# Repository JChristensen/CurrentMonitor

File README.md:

# Current Monitor
https://github.com/JChristensen/CurrentMonitor  
README file  
Jack Christensen  
Aug-2018

## License
  
Current Monitor by Jack Christensen is licensed under a [Creative Commons Attribution-ShareAlike 4.0 International License](http://creativecommons.org/licenses/by-sa/4.0/).

## Overview
The Current Monitor is an Arduino Uno-compatible board designed to function as a sensor node in an XBee network. While the board was primarily designed to interface to current transformers, it is also general enough to have wider applicability. Features include:
- ATmega328P microcontroller
- interface circuitry for two current transformers
- two analog pins (for current transformers) and four digital pins brought out to screw-type terminal blocks
- three on-board LEDs
- interface circuitry and 3.3V supply for the XBee module
- powered from most any 7-12VDC wall wart with a 2.5mm plug

[Hardware design](https://github.com/JChristensen/CurrentMonitor) and [an Arduino Current Transformer library](https://github.com/JChristensen/CurrentTransformer) are available on GitHub.  
PC boards can be ordered from [OSH Park](https://www.oshpark.com/shared_projects/QCjudQBh).  
A bill of materials is available at [Mouser Electronics](https://www.mouser.com/ProjectManager/ProjectDetail.aspx?State=EDIT&ProjectGUID=d999f360-1612-415f-8324-2acceb9dd570) and also in the [GitHub repo](https://github.com/JChristensen/CurrentMonitor).

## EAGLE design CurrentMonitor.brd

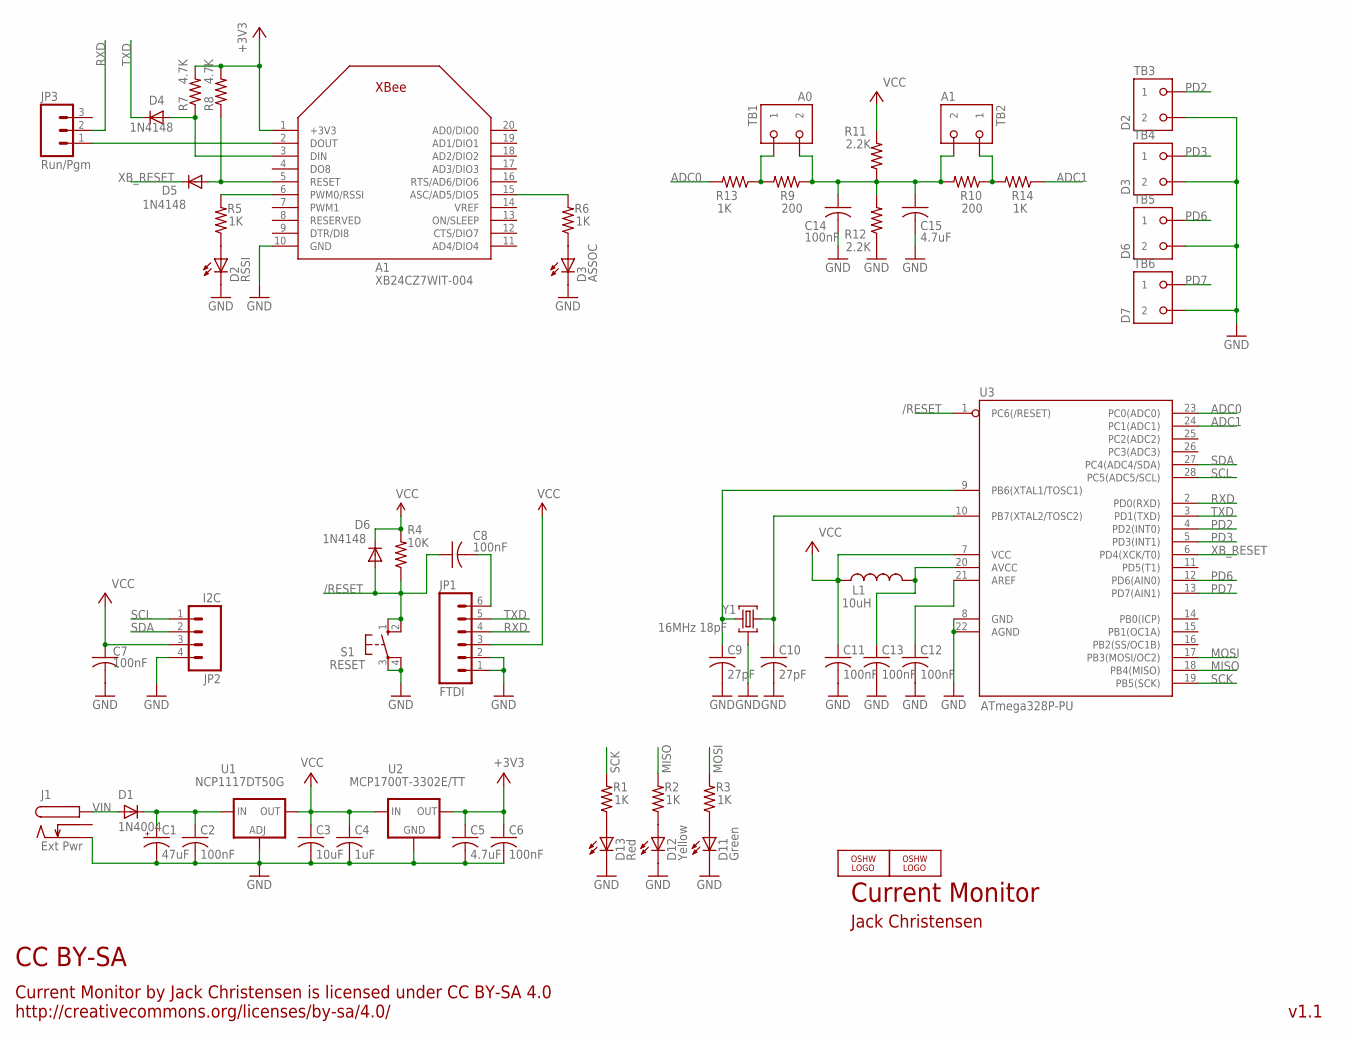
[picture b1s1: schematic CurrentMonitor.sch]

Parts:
A1: XB24CZ7WIT-004; XBEE_OVAL_PADS
C1: 47uF; E5-5
C2, C6, C7, C8, C11, C12, C13, C14: 100nF; M0805
C3: 10uF; M0805
C4: 1uF; M0805
C5, C15: 4.7uF; M0805
C9, C10: 27pF; M0805
D1: 1N4004; 1N400X
D2: RSSI; D0805A
D3: ASSOC; D0805
D4, D5: 1N4148; SOD-323F-A
D6: 1N4148; SOD-323F
D11: Green; D0805
D12: Yellow; D0805
D13: Red; D0805
J1: Ext Pwr; KLDX-0202
JP1: FTDI; 1X06_LOCK
JP2: I2C; 1X04_LOCK
JP3: Run/Pgm; 1X03_LOCK
L1: 10uH; M0805
LOGO1, LOGO2: OSHW_LOGO_8MILX0100-NT; OSHW_8X100_NOTEXT
R1, R2, R3, R5, R6, R13, R14: 1K; M0805
R4: 10K; M0805
R7, R8: 4.7K; M0805
R9, R10: 200; M0805
R11, R12: 2.2K; M0805
S1: RESET; B3F-10XXOCT
TB1: A0; OST-TB-2-3.5MM
TB2: A1; OST-TB-2-3.5MM
TB3: D2; OST-TB-2-3.5MM
TB4: D3; OST-TB-2-3.5MM
TB5: D6; OST-TB-2-3.5MM
TB6: D7; OST-TB-2-3.5MM
U1: NCP1117DT50G; DPACK
U2: MCP1700T-3302E/TT; SOT23-W
U3: ATmega328P-PU; DIL28-3
Y1: 16MHz 18pF; RESONATOR

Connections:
+3V3: A1.1 (+3V3), C5.1, C6.1, R7.2, R8.2, U2.2 (OUT)
/RESET: C8.1, D6.A, R4.1, S1.1 (S), S1.2 (S1), U3.1 (PC6(/RESET))
ADC0: R13.2, U3.23 (PC0(ADC0))
ADC1: R14.1, U3.24 (PC1(ADC1))
GND: A1.10 (GND), C1.-, C2.2, C3.2, C4.2, C5.2, C6.2, C7.2, C9.2, C10.2, C11.2, C12.2, C13.2, C14.2, C15.2, D2.K (C), D3.K (C), D11.K (C), D12.K (C), D13.K (C), J1.P$2, JP1.1, JP1.2, JP2.4, R12.1, S1.3, S1.4 (P1), TB3.P$2 (2), TB4.P$2 (2), TB5.P$2 (2), TB6.P$2 (2), U1.1 (ADJ), U2.1 (GND), U3.8 (GND), U3.22 (AGND), Y1.2
MISO: R2.2, U3.18 (PB4(MISO))
MOSI: R3.2, U3.17 (PB3(MOSI/OC2))
unnamed: D13.A, R1.1
unnamed: D1.A, J1.P$1
unnamed: C14.1, C15.1, R9.1, R10.2, R11.1, R12.2, TB1.P$2 (2), TB2.P$2 (2)
unnamed: C10.1, U3.10 (PB7(XTAL2/TOSC2)), Y1.3
unnamed: C13.1, L1.2, U3.20 (AVCC)
unnamed: C9.1, U3.9 (PB6(XTAL1/TOSC1)), Y1.1
unnamed: C12.1, U3.21 (AREF)
unnamed: A1.3 (DIN), D4.A, R7.1
unnamed: D12.A, R2.1
unnamed: A1.2 (DOUT), JP3.1
unnamed: D2.A, R5.1
unnamed: D3.A, R6.1
unnamed: A1.6 (PWM0/RSSI), R5.2
unnamed: A1.15 (ASC/AD5/DIO5), R6.2
unnamed: R9.2, R13.1, TB1.P$1 (1)
unnamed: R10.1, R14.2, TB2.P$1 (1)
unnamed: A1.5 (RESET), D5.A, R8.1
unnamed: D11.A, R3.1
PD2: TB3.P$1 (1), U3.4 (PD2(INT0))
PD3: TB4.P$1 (1), U3.5 (PD3(INT1))
PD6: TB5.P$1 (1), U3.12 (PD6(AIN0))
PD7: TB6.P$1 (1), U3.13 (PD7(AIN1))
RST: C8.2, JP1.6
RXD: JP1.4, JP3.2, U3.2 (PD0(RXD))
SCK: R1.2, U3.19 (PB5(SCK))
SCL: JP2.1, U3.28 (PC5(ADC5/SCL))
SDA: JP2.2, U3.27 (PC4(ADC4/SDA))
TXD: D4.K, JP1.5, U3.3 (PD1(TXD))
VCC: C3.1, C4.1, C7.1, C11.1, D6.K, JP1.3, JP2.3, L1.1, R4.2, R11.2, U1.4 (OUT), U2.3 (IN), U3.7 (VCC)
VIN: C1.+, C2.1, D1.K, U1.3 (IN)
XB_RESET: D5.K, U3.6 (PD4(XCK/T0))

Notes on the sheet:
Current Monitor
Jack Christensen
Current Monitor by Jack Christensen is licensed under CC BY-SA 4.0 http://creativecommons.org/licenses/by-sa/4.0/
CC BY-SA
v1.1

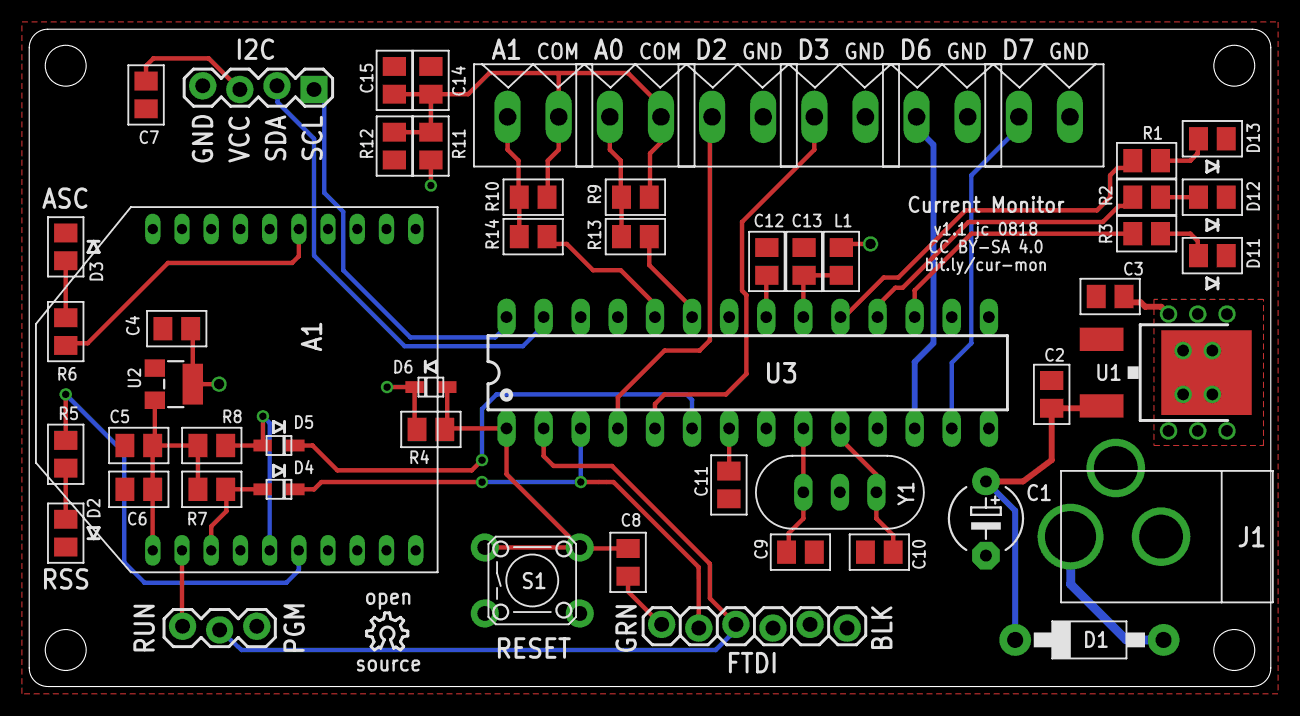
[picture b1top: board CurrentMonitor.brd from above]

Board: 2 copper layers, 85.0 x 45.0 mm, 57 parts (1 on the bottom side), 38 nets.

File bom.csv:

Current Monitor,,,,,
Bill of materials,,,,,
https://www.mouser.com/ProjectManager/ProjectDetail.aspx?Acc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,,,,,
,,,,,
Part No.,Order Qty.,Mouser #,Mfr. #,Manufacturer,Description
A1,2,855-M22-7131042,M22-7131042,Harwin,Headers & Wire Housings 10 PIN SIL VERTICAL GOLD+TIN SOCKET
A1,1,888-XB24CZ7WIT-004,XB24CZ7WIT-004,Digi International,Zigbee Modules (802.15.4) XBee ZB S2C TH Wire Antenna
C1,1,667-ECA-1CM470B,ECA-1CM470B,Panasonic,Aluminum Electrolytic Capacitors - Radial Leaded Al Lytic Cap 85C Radial M Series
"C2, C6, C7, C8, C11-14",8,581-08053C104K,08053C104KAT2A,AVX,Multilayer Ceramic Capacitors MLCC - SMD/SMT 25V .1uF X7R 0805 10%
C3,1,963-LMK212BJ106KG-T,LMK212BJ106KG-T,Taiyo Yuden,Multilayer Ceramic Capacitors MLCC - SMD/SMT 10uF 10V X5R +/-10% 0805 Gen Purp
C4,1,81-GRM21BR61C105KA1K,GRM21BR61C105KA01K,Murata,Multilayer Ceramic Capacitors MLCC - SMD/SMT 1uf 16V X5R +/-10% 0805
"C5, C15",2,963-LMK212B7475KG-T,LMK212B7475KG-T,Taiyo Yuden,Multilayer Ceramic Capacitors MLCC - SMD/SMT 4.7uF 10V X7R +/-10% 0805 Gen Purp
"C9, C10",2,603-CC805JRNPO9BN270,CC0805JRNPO9BN270,Yageo,Multilayer Ceramic Capacitors MLCC - SMD/SMT 27pF 50V NPO 5%
D1,1,863-1N4004G,1N4004G,ON Semiconductor,Rectifiers 400V 1A Standard
D12,1,859-LTST-C171KSKT,LTST-C171KSKT,Lite-On,Standard LEDs - SMD Yellow Clear 587nm
"D2, D13",2,859-LTST-C171KRKT,LTST-C171KRKT,Lite-On,Standard LEDs - SMD Red Clear 55MCD
"D3, D11",2,859-LTST-C171KGKT,LTST-C171KGKT,Lite-On,Standard LEDs - SMD Green Clear 571nm
"D4, D5, D6",3,512-1N4148WS,1N4148WS,ON Semiconductor,"Diodes - General Purpose, Power, Switching Small Signal Diode"
J1,1,806-KLDX-0202-B,KLDX-0202-B,Kycon,DC Power Connectors 2.5mm PCB JACK POWER JACK
JP1,1,,,,"0.1” Header, male, 6-position"
JP2,1,,,,"0.1” Header, female, 4-position"
JP3,1,,,,"0.1” Header, male, 3-position"
JP3,1,,,,Shorting block for 0.1” header
L1,1,963-LBR2012T100K,LBR2012T100K,Taiyo Yuden,Fixed Inductors 0805 10uH 468mOhms +/-10%Tol 150mA
"R1-3, R5-6, R13-14",7,603-RC0805FR-071KL,RC0805FR-071KL,Yageo,Thick Film Resistors - SMD 1K OHM 1%
"R11, R12",2,603-RC0805FR-072K2L,RC0805FR-072K2L,Yageo,Thick Film Resistors - SMD 2.2K OHM 1%
R4,1,603-RC0805FR-1310KL,RC0805FR-1310KL,Yageo,Thick Film Resistors - SMD 10K OHM 1%
"R7, R8",2,603-RC0805FR-074K7L,RC0805FR-074K7L,Yageo,Thick Film Resistors - SMD 4.7K OHM 1%
"R9, R10",2,603-RC0805FR-07200RL,RC0805FR-07200RL,Yageo,Thick Film Resistors - SMD 200 OHM 1%
S1,1,653-B3F-1020,B3F-1020,Omron,Tactile Switches 6X6 Flat 5mm Btn Force 100g w/o Grd
"TB1/2, TB3/4, TB5/6",3,651-1984633,1984633,Phoenix Contact,Fixed Terminal Blocks PT 1.5/4-3.5H 4POS HRZ 3.5mm SCREW
U1,1,863-NCP1117DT50G,NCP1117DT50G,ON Semiconductor,LDO Voltage Regulators 5.0V 1A Positive
U2,1,579-MCP1700T3302E/TT,MCP1700T-3302E/TT,Microchip,LDO Voltage Regulators 250mA Adj LDO 2%
U3,1,556-ATMEGA328P-PU,ATMEGA328P-PU,Microchip,8-bit Microcontrollers - MCU 32KB In-system Flash 20MHz 1.8V-5.5V
Y1,1,815-ABL-16-B4Y,ABL-16.000MHz-B4Y,ABRACON,"Crystals 16.000MHZ, 18pF 30ppm -20C +70C"

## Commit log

2018-08-29 Initial commit.
2018-08-29 Add terminal blocks for additional GPIO and LEDs.
2018-08-29 Layout tweaks.
2018-08-29 Enlarge via for Vcc.
2018-08-29 Change Run/Pgm header to "lock" package.
2018-08-30 Minor board layout tweaks.
2018-08-30 Update README and LICENSE files.
2018-09-04 Add bill of materials.
2018-10-01 Update README, add photos.

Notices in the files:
parts and their libraries:
SparkFun: Licensing: CC v3.0 Share-Alike You are welcome to use this library for commercial purposes.
